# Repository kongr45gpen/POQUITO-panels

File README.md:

# PocketQube Solar Power Board

A modification of the [Libre Space Foundation QUBIK solar panels](https://gitlab.com/librespacefoundation/qubik/qubik-spb/-/tree/master?ref_type=heads) with a magnetorquer and a coarse sun sensor.

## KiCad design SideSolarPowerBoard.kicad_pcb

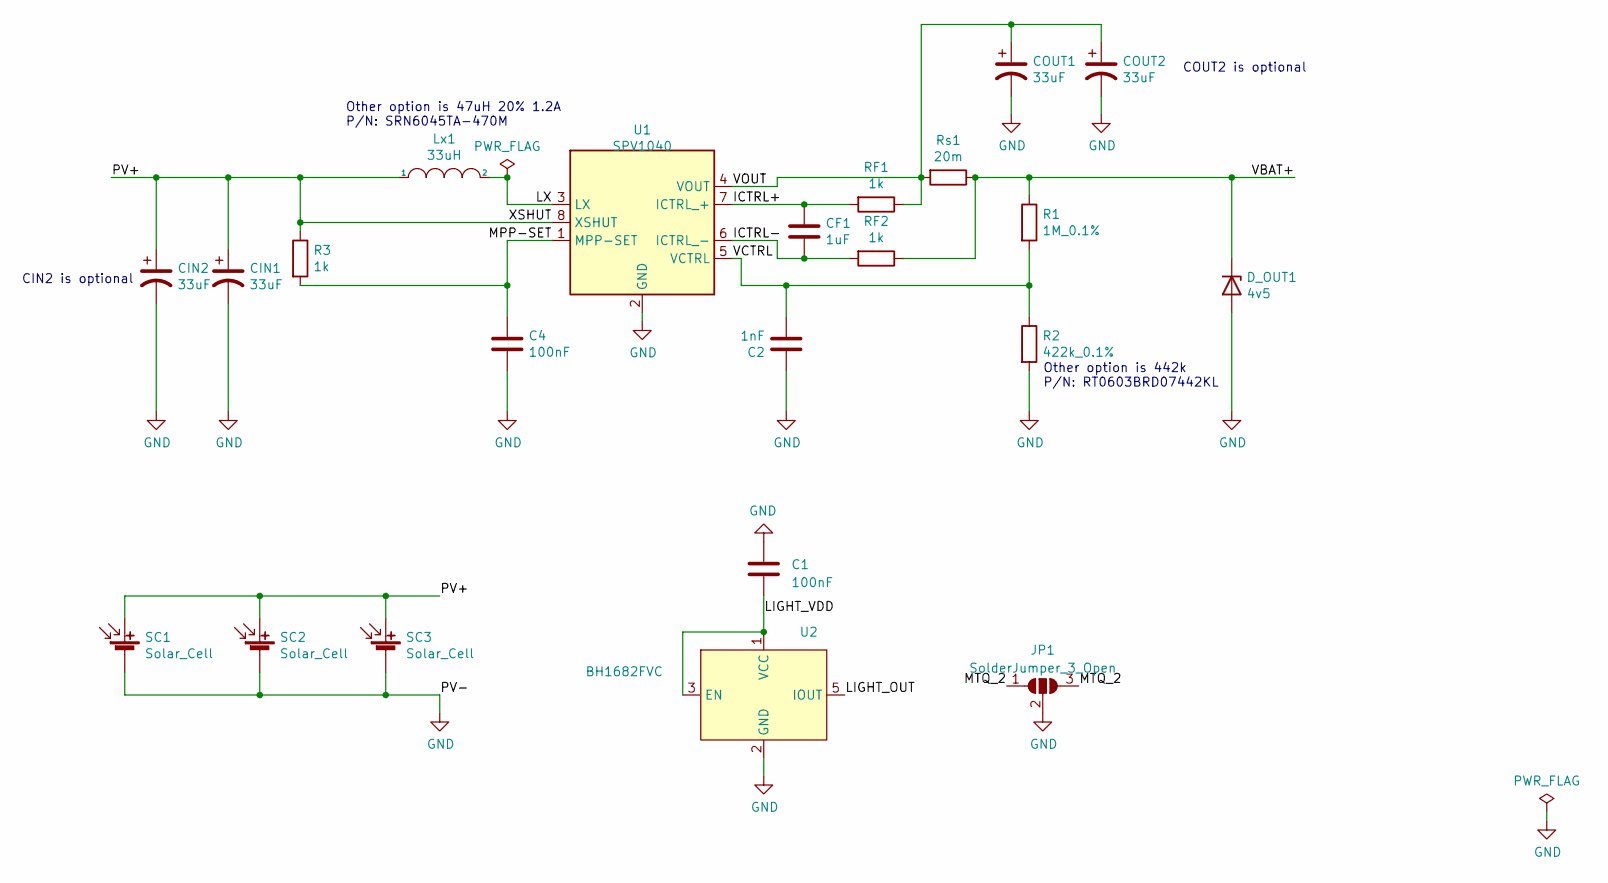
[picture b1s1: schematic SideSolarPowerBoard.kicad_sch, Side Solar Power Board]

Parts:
C1: 100nF; C_0402_1005Metric_Pad0.74x0.62mm_HandSolder; MPN C0402C104K8RACTU
C2: 1nF; C_0603_1608Metric; MPN C0603C102J8HACTU
C4: 100nF; C_0603_1608Metric; MPN C0603C104K8RACTU
CF1: 1uF; C_0603_1608Metric; MPN C0603C105M8RACAUTO
CIN1, CIN2: 33uF; C_0805_2012Metric; MPN C2012X5R1A336M125AC
COUT1, COUT2: 33uF; C_0805_2012Metric; MPN C2012X5R1A336M125AC
D_OUT1: 4v5; DO-222AA; MPN SMM4F5.0A-TR
JP1: SolderJumper_3_Open; SolderJumper-3_P1.3mm_Open_RoundedPad1.0x1.5mm_NumberLabels
Lx1: 33uH; L_Bourns_SRN6045TA; MPN SRN6045TA-330M
R1: 1M_0.1%; R_0603_1608Metric; MPN RN73H1JTTD1004B25
R2: 422k_0.1%; R_0603_1608Metric; MPN RN73H1JTTD4223B25
R3: 1k; R_0603_1608Metric; MPN CRCW06031K00FKEA
RF1, RF2: 1k; R_0603_1608Metric; MPN CRCW06031K00FKEA
Rs1: 20m; R_0603_1608Metric; MPN RCWE060320L0FQEA
SC1, SC2, SC3: Solar_Cell; SM141K04LV; MPN SM141K04LV
U1: SPV1040; TSSOP-8_4.4x3mm_P0.65mm; MPN SPV1040TTR
U2: BH1682FVC; WSOF-5; MPN BH1682FVC-TR

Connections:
/ICTRL+: CF1.1, RF1.2, U1.7 (ICTRL_+)
/ICTRL-: CF1.2, RF2.2, U1.6 (ICTRL_-)
/LIGHT_OUT: U2.5 (IOUT)
/LIGHT_VDD: C1.1, U2.1 (VCC), U2.3 (EN)
/LX: Lx1.2, U1.3 (LX)
/MPP-SET: C4.1, R3.2, U1.1 (MPP-SET)
/MTQ_2: JP1.1 (A), JP1.3 (B)
/PV+: CIN1.1, CIN2.1, Lx1.1, R3.1, SC1.1 (+), SC2.1 (+), SC3.1 (+), U1.8 (XSHUT)
/VBAT+: D_OUT1.1 (K), R1.1, RF2.1, Rs1.1
/VCTRL: C2.2, R1.2, R2.1, U1.5 (VCTRL)
/VOUT: COUT1.1, COUT2.1, RF1.1, Rs1.2, U1.4 (VOUT)
GND: C1.2, C2.1, C4.2, CIN1.2, CIN2.2, COUT1.2, COUT2.2, D_OUT1.2 (A), JP1.2 (C), R2.2, SC1.2 (-), SC2.2 (-), SC3.2 (-), U1.2 (GND), U2.2 (GND)

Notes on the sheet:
Other option is 47uH 20% 1.2A P/N: SRN6045TA-470M
CIN2 is optional
COUT2 is optional
Other option is 442k P/N: RT0603BRD07442KL

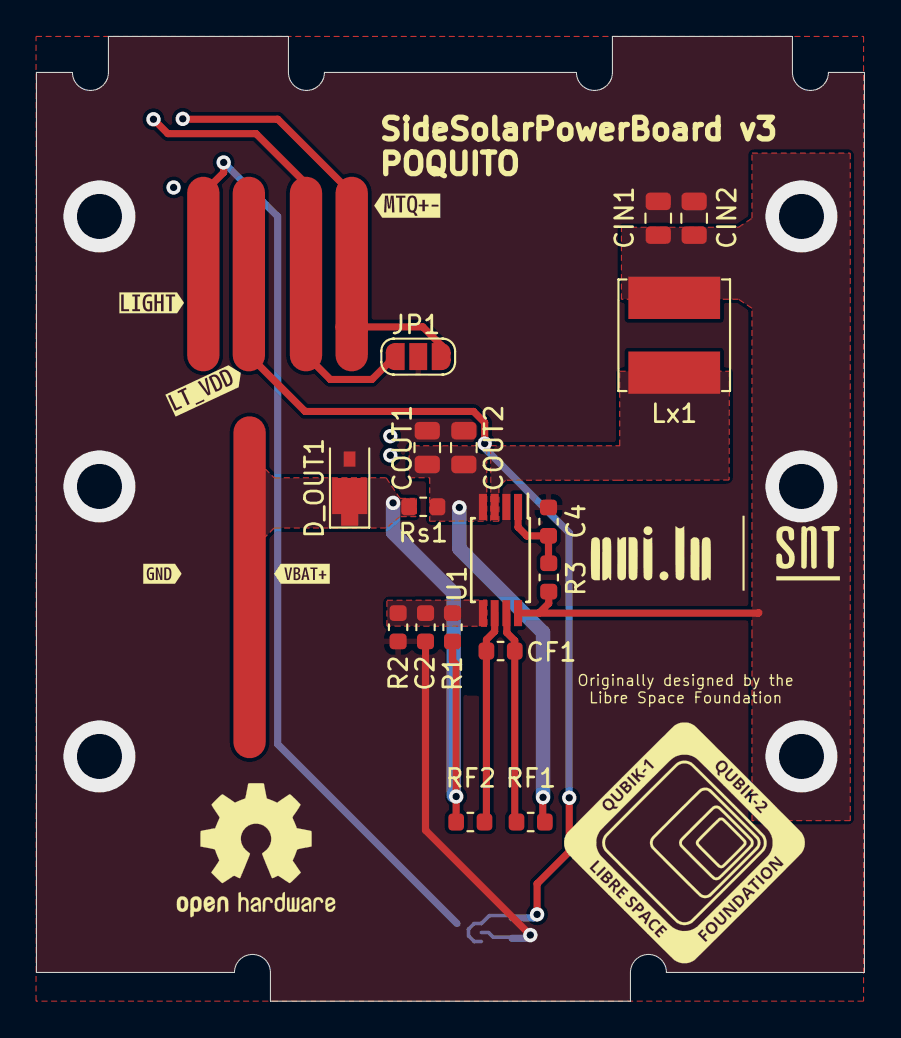
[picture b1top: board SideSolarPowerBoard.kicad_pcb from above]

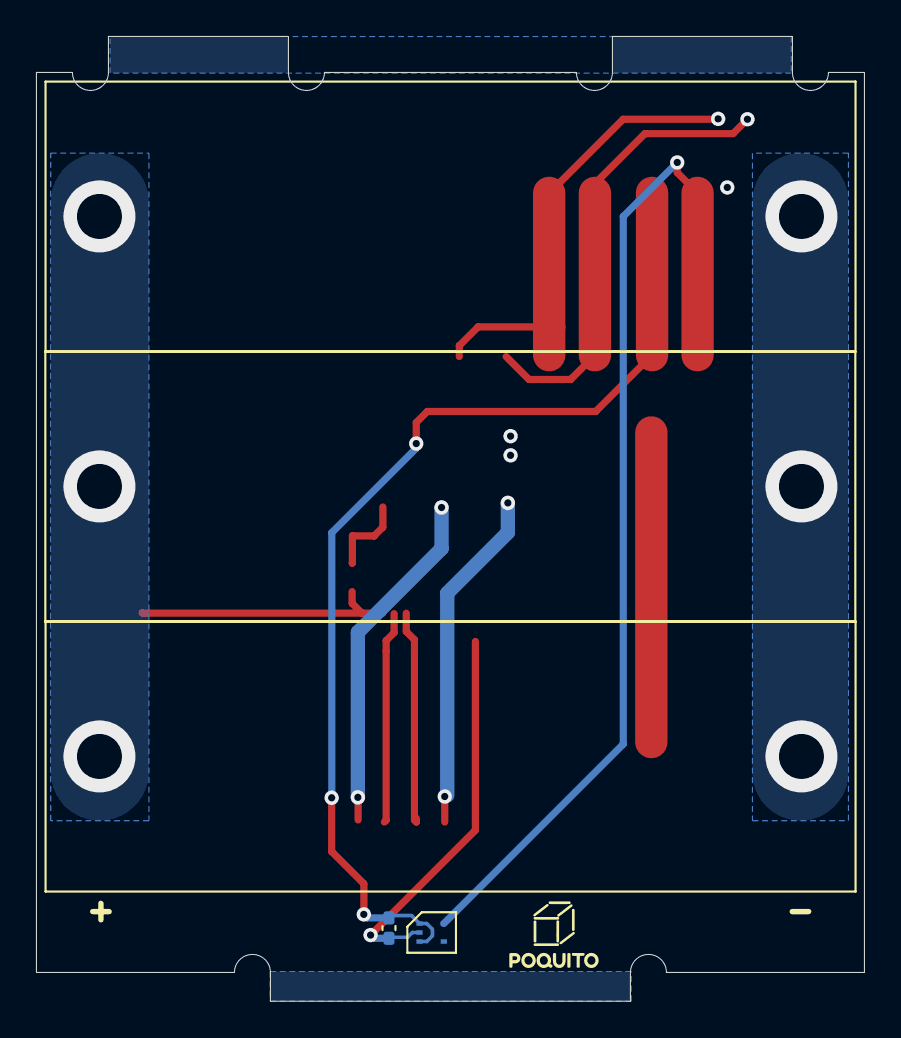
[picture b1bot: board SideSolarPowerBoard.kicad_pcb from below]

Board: 6 copper layers, 46.0 x 53.6 mm, 27 parts (5 on the bottom side), 11 nets.

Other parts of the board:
kibuzzard-64FE2F6D: G***; kibuzzard-64FE2F6D
kibuzzard-64FE2F42: G***; kibuzzard-64FE2F42
kibuzzard-658D61DC: G***; kibuzzard-658D61DC
kibuzzard-658D6171: G***; kibuzzard-658D6171
kibuzzard-658D6185: G***; kibuzzard-658D6185

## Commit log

2023-09-07 Migrate project to KiCad 7
2023-09-07 Quickly add a sensor and a connector
2023-09-10 Move new kicad_pcb file
2023-09-10 Add all missing connections
2023-09-10 Add logos
2023-09-10 Fix connection of MTQ2 to not overlap run
2023-09-11 Update modifications in LICENSE
2023-12-28 Update to pogo pin ADCS design
2023-12-28 Fix position of Lx

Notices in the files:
SideSolarPowerBoard.kicad_sch:
CERN Open Hardware Licence Version 2 - Weakly Reciprocal
